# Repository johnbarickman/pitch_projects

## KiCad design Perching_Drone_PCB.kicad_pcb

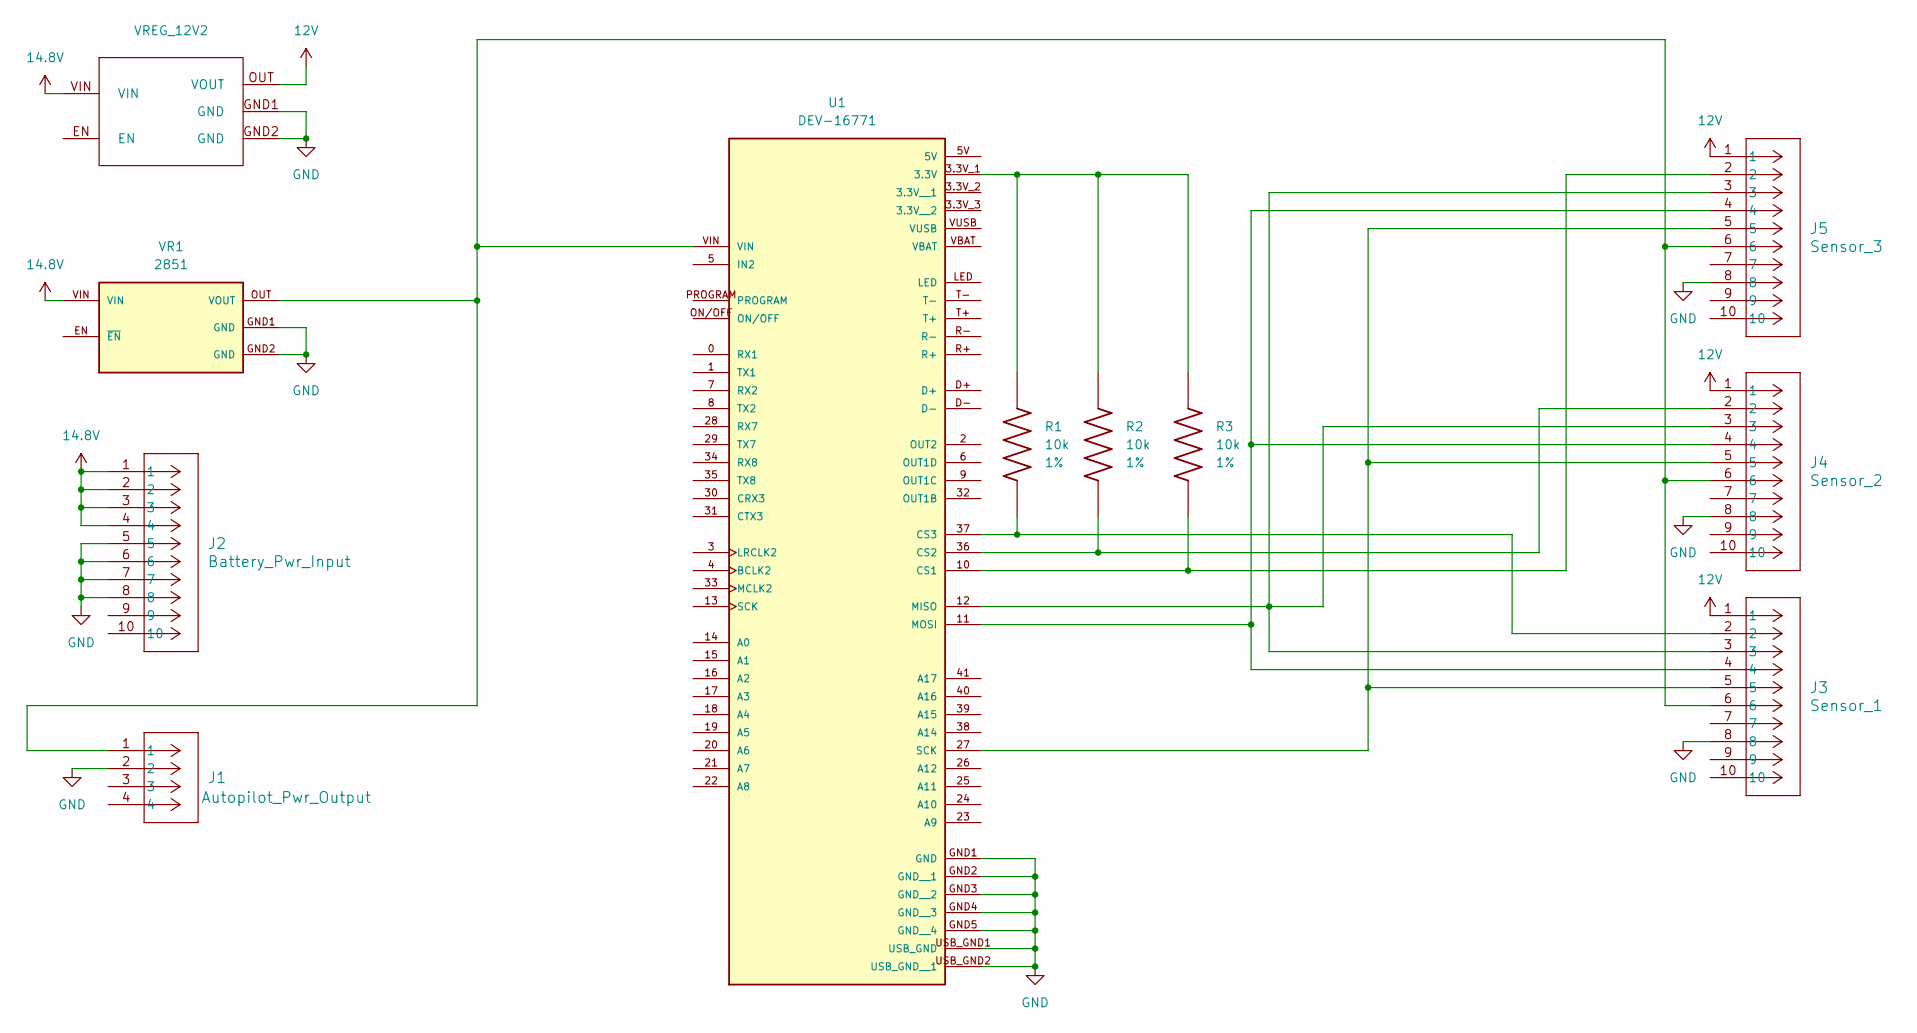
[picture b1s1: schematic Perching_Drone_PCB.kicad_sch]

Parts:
J1: Autopilot_Pwr_Output; 2Pin_Molex
J2: Battery_Pwr_Input; 8Pin_Molex
J3: Sensor_1; 8Pin_Molex
J4: Sensor_2; 8Pin_Molex
J5: Sensor_3; 8Pin_Molex
R1, R2, R3: 10k; R_0402_1005Metric; Tolerance 1%; PARTREV 3/1/2020
U1: DEV-16771; MODULE_DEV-16771; PARTREV 4.1
VR1: 2851; VREG_2851
VREG_12V2: VREG_2851

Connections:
12V: J3.1, J4.1, J5.1, VREG_12V2.OUT (VOUT)
14.8V: J2.1, J2.2, J2.3, J2.4, VR1.VIN, VREG_12V2.VIN
GND: J1.2, J2.5, J2.6, J2.7, J2.8, J3.8, J4.8, J5.8, U1.GND1 (GND), U1.GND2 (GND__1), U1.GND3 (GND__2), U1.GND4 (GND__3), U1.GND5 (GND__4), U1.USB_GND1 (USB_GND), U1.USB_GND2 (USB_GND__1), VR1.GND1 (GND), VR1.GND2 (GND), VREG_12V2.GND1 (GND), VREG_12V2.GND2 (GND)
unnamed: J3.5, J4.5, J5.5, U1.27 (SCK)
unnamed: R1.2, R2.2, R3.2, U1.3.3V_1 (3.3V)
unnamed: J5.2, R3.1, U1.10 (CS1)
unnamed: J4.2, R2.1, U1.36 (CS2)
unnamed: J3.2, R1.1, U1.37 (CS3)
unnamed: J3.3, J4.3, J5.3, U1.12 (MISO)
unnamed: J3.4, J4.4, J5.4, U1.11 (MOSI)
unnamed: J1.1, J3.6, J4.6, J5.6, U1.VIN, VR1.OUT (VOUT)

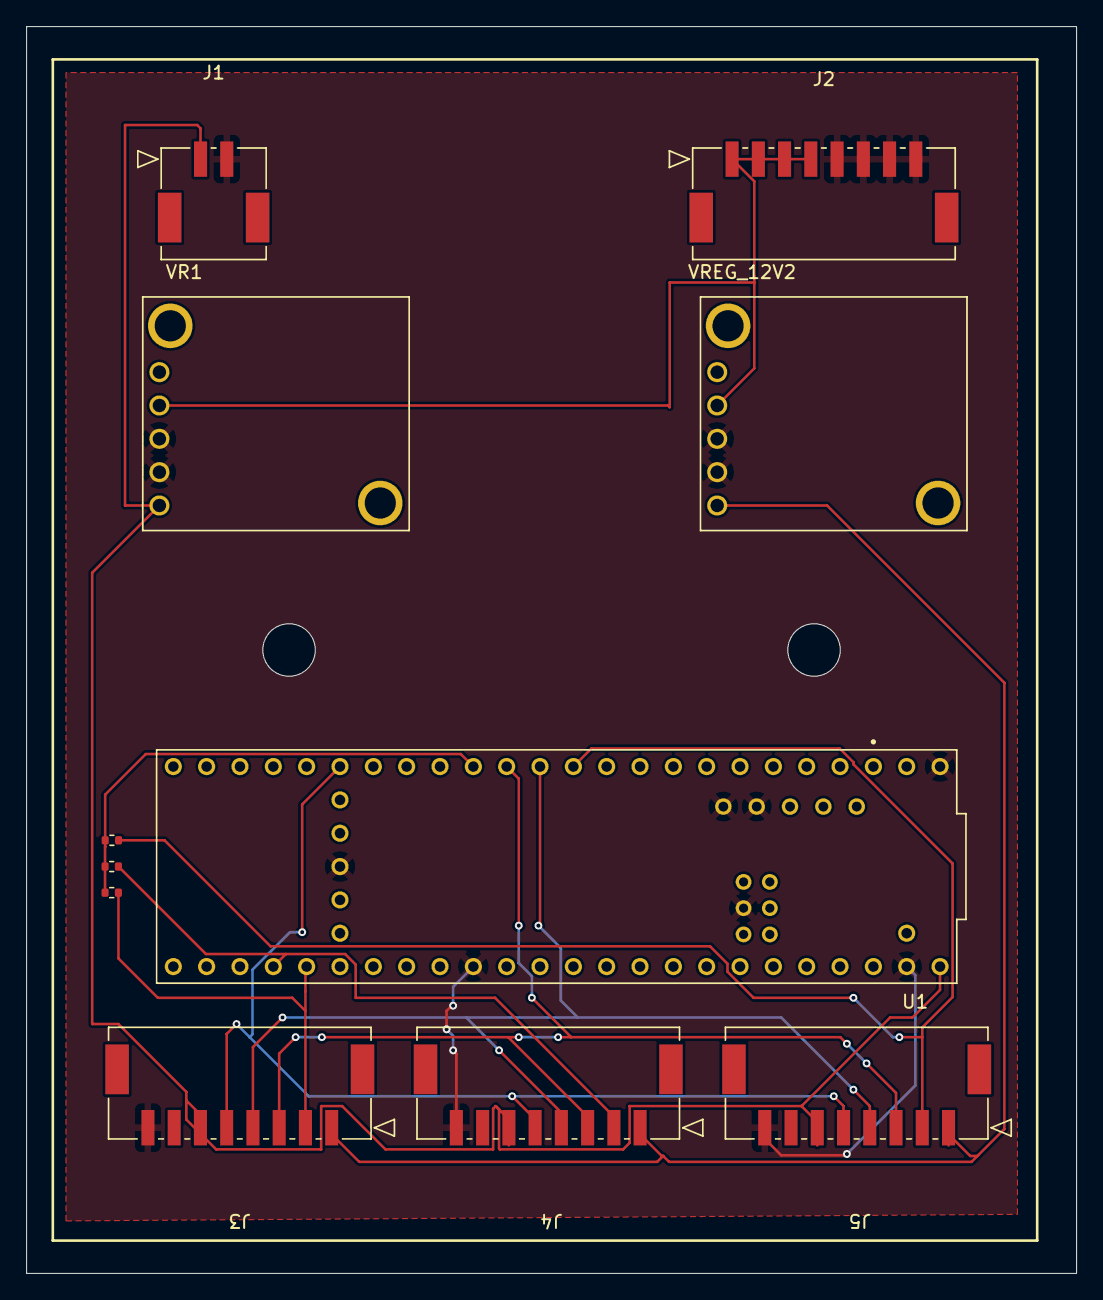
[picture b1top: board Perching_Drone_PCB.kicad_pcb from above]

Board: 2 copper layers, 80.0 x 95.0 mm, 11 parts (0 on the bottom side), 11 nets.

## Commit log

2024-06-12 ArmyDrone_PD_PCB
